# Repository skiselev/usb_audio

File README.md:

# Compact USB Audio Adapter

## Introduction
I was looking for a USB audio adapter for my Intel Galileo projects, and surprisingly I was not able to find a compact USB audio adapter which will offer line input or digital (optical) input and output. Most USB audio dongles available on the market are intended to be used with a headset and only offer monophonic microphone input. One exception was Behringer UCA202 which is bulky for my projects. And so I've designed this adapter.

## Overview
This USB Audio adapter can be used with small SBCs like Intel Galileo, Raspberry Pi, or BeagleBone Black to provide high quality audio input and output. Its size is only 2.1 x 1.6 inches (53.44 x 40.74 mm). This USB Audio adapter will also work with regular PCs, Android based smartphones and tablets, or almost everything else that supports USB audio. It is based on popular Texas Instruments (was Burr Brown) PCM2902C, and schematic mostly follows Texas Instrument's reference design.

### Photos
#### Top side

#### Bottom side

## Design
As mentioned above the main component is Texas Instruments PCM2902 USB audio codec IC (U1). Additionally the circuit uses Texas Instruments REG103UA LDO IC for conditioning power for the analog circuitry (U2) and a pair of dual channel operational amplifier ICs that work as low pass filters for input and output (U5 and U6).

### Schematic and PCB Layout

[Schematic - Version 2.0](KiCad/USB_Audio-Schematic-2.0.pdf)

[PCB Layout - Version 2.0](KiCad/USB_Audio-Board-2.0.pdf)

### Design Modifications and Components' Substitution
There is a lot of flexibility in the design:
* The USB audio codec IC (U1) can be PCM2902, PCM2906, PCM2900, and PCM2904.
  * PCM2902 and PCM2906 provide S/PDIF digital interface. PCM2900 and PCM2904 do not provide it.
  * The difference between PCM2902 and PCM2906 or between PCM2900 and PCM2904 is very subtle: PCM2900 and PCM2902 specify 100mA as Maxpower value in USB descriptor, while PCM2904 and PCM2906 specify 500mA. Operating systems should be using Maxpower values to estimate power consumption by the attached USB devices and disconnect USB devices if host is unable to supply enough power.
  * If using codec without S/PDIF support the components related to optical input and output should not be mounted.
  * I used the latest PCM290xC revision. Other, older revisions don't differ significantly and can be used as well.
* The REG103 LDO (U2) is optional and can be removed to lower the cost at some audio quality degradation. It is also possible to replace it with cheaper LDO with minor schematic and PCB modifications.
* The design uses high-speed operational amplifiers. Either one of these op amps or both can be bypassed, leaving just 100 ohm / 10 uF capacitors for audio coupling. It is also possible to use other compatible operational amplifiers (important characteristics: single power supply 3.3V, rail-to-rail)
* Both input and output parts are optional. For example if only ADC part is needed, no need to assemble components related to audio output. Same applies for DAC only (audio output only) use. In this case I suggest grounding audio inputs of PCM2902 to avoid noise.
* The PCB supports two options for connecting to USB:
  * Using Micro USB connector
  * Using 5-pin header (it is also possible to solder a USB cable directly to the board instead of this header).
* Volume control buttons are optional

### Assembly Notes
Due to project's size and component availability the project mostly uses SMT components. I used through hole components for components that are subject to physical stress (connectors and buttons). It it is not too difficult to solder SMT components it with some practice. Here are some tips:

* Have a well lighten workspace.
* Use a low power (25W or so) soldering iron with thin tip, better yet a temperature controlled soldering station. Keep the tip of soldering iron clean.
* Use thin solder with flux. Have some desoldering braid to remove accidental solder bridges or excess solder.
* I found it convenient first to put some solder on a first pad of a component (or on two opposite pads in case of an IC. When put the component using tweezers and heat the pad at the same time. Next double check component orientation and solder remaining pads. Note that diodes and tantalum capacitors are polarized, so the orientation is important.
* Solder ICs first, next solder micro USB connector.
* After that solder all the resistors, inductor, and smaller (0603 and 0805) capacitors on the top side, going from ICs to sides of the board.
* Solder Schottky diode, LED, crystal resonator, and tantalum capacitors. Make sure to check that they are oriented properly.
* Turn the board up side down, and solder resistors and the capacitors on the bottom side.
* Finally solder through hole components: connectors, optical modules, buttons.
* Clean the flux remains with some alcohol. (Be careful not to get alcohol/flux inside optical modules, or maybe solder them after cleaning the board).
* Search the Internet for SMT soldering tutorials.

### Bill of Materials
[USB Audio project on Mouser.com](http://www.mouser.com/ProjectManager/ProjectDetail.aspx?AccessID=4c01b1b0e1) - View and order all components except of the PCB, screws and nuts.

[USB Audio project on OSH Park](http://oshpark.com/shared_projects/Dffqy1VF) - View and order PCB.

Component type     | Reference | Description                                 | Quantity | Possible sources and notes
------------------ | --------- | ------------------------------------------- | -------- | --------------------------
PCB                |           | USB Audio PCB - V2                          | 1        | Order at [OSH Park](http://oshpark.com/shared_projects/Dffqy1VF) or from any other PCB manufacturer using Gerber files from [gerber](gerber) folder.
Capacitor          | C1 - C3   | 22pF C0G SMT 0603 capacitor                 | 3        | Mouser [77-VJ0603A220JXACBC](https://www.mouser.com/ProductDetail/77-VJ0603A220JXACBC). Note: C3 is not needed if not implementing optical S/PDIF input.
Capacitor          | C4 - C7   | 330pF C0G SMT 0805 capacitor                | 4        | Mouser [77-VJ0805A331KXACBC](https://www.mouser.com/ProductDetail/77-VJ0805A331KXACBC)
Capacitor          | C8 - C11  | 1.8nF C0G SMT 0805 capacitor                | 4        | Mouser [81-GRM215C1H182JA01D](https://www.mouser.com/ProductDetail/81-GRM215C1H182JA01D)
Capacitor          | C12, C13  | 100nF X7R SMT 0805 capacitor                | 2        | Mouser [80-C0805C104K3R7210](https://www.mouser.com/ProductDetail/80-C0805C104K3R7210]. Note: These capacitor are not needed if not implementing optical S/PDIF input and output.
Capacitor          | C14 - C20 | 1uF X7R SMT 0805 capacitor                  | 7        | Mouser [80-C0805C105K4R](https://www.mouser.com/ProductDetail/80-C0805C105K4R]
Capacitor          | C21 - C30 | 10uF tantalum SMT capacitor                 | 10       | Mouser [74-593D106X9016A2TE3](https://www.mouser.com/ProductDetail/74-593D106X9016A2TE3)
Capacitor          | C31, C32  | 220uF tantalum SMT capacitor                | 2        | Mouser [581-TLNT227M010R1300](https://www.mouser.com/ProductDetail/581-TLNT227M010R1300). Note: Use the recommended value if driving low impedance loads (for example headphones). For high impedance loads (e.g. line output connected to an amplifier) cheaper 10uF capacitors can be used. See previous line for part number.
Schottky Diode     | D1        | Schottky diode with low voltage drop (350mV) | 1       | Mouser [771-PMEG2010ER115](https://www.mouser.com/ProductDetail/771-PMEG2010ER115)
LED                | D2        | 0603 LED                                    | 1        | Mouser [78-VLMTG1300-GS08](https://www.mouser.com/ProductDetail/78-VLMTG1300-GS08). Any color can be used :-) The suggested part is "pure" green. It is too bright to my taste, so if using it consider increasing value of R8. Or use "conventional" green and save a few cents.
Inductor           | L1        | 47uH SMT 0805 inductor                      | 1        | Mouser [963-LBR2012T470K](https://www.mouser.com/ProductDetail/963-LBR2012T470K). Note: This inductor is not needed if not implementing optical S/PDIF input.
Connector          | P1        | Micro USB receptacle with through hole pegs | 1        | Mouser [649-10118194-0001LF](https://www.mouser.com/ProductDetail/649-10118194-0001LF). Note: Use either P1 or P2
Connector          | P2        | Pin Header 5x1, 2.54 mm lead spacing        | 1        | Mouser [649-68000-105HLF](https://www.mouser.com/ProductDetail/649-68000-105HLF). Note: Use either P1 or P2
Connector          | P3        | 3.5 mm stereo audio jack, blue              | 1        | Mouser [806-STX-31203B284C](https://www.mouser.com/ProductDetail/806-STX-31203B284C)
Connector          | P4        | 3.5 mm stereo audio jack, green             | 1        | Mouser [806-STX-31203B577C](https://www.mouser.com/ProductDetail/806-STX-31203B577C)
Resistor           | R1 - R3   | 2.2 ohm 1% SMT 0603 resistor                | 3        | Mouser [71-CRCW0603-2.2-E3](https://www.mouser.com/ProductDetail/71-CRCW0603-2.2-E3). Note: For R2 and R3 use the recommended value if driving low impedance loads. For high impedance load resistance can be increased to 100 ohm. See R6, R7 line for part number.
Resistor           | R4, R5    | 22 ohm 1% SMT 0603 resistor                 | 2        | Mouser [71-CRCW0603-22-E3](https://www.mouser.com/ProductDetail/71-CRCW0603-22-E3)
Resistor           | R6, R7    | 100 ohm 1% SMT 0603 resistor                | 2        | Mouser [71-CRCW0603100RFKEB](https://www.mouser.com/ProductDetail/71-CRCW0603100RFKEB)
Resistor           | R8        | 470 ohm 1% SMT 0603 resistor                | 1        | Mouser [71-CRCW0603470RFKEB](https://www.mouser.com/ProductDetail/71-CRCW0603470RFKEB)
Resistor           | R9 - R12  | 1.5 Kohm 1% SMT 0603 resistor               | 4        | Mouser [71-CRCW0603-1.5K-E3](https://www.mouser.com/ProductDetail/71-CRCW0603-1.5K-E3)
Resistor           | R13 - R16 | 3.9 Kohm 1% SMT 0603 resistor               | 4        | Mouser [71-CRCW0603-3.9K-E3](https://www.mouser.com/ProductDetail/71-CRCW0603-3.9K-E3)
Resistor           | R17 - R24 | 12 Kohm 1% SMT 0603 resistor                | 8        | Mouser [71-CRCW0603-12K-E3](https://www.mouser.com/ProductDetail/71-CRCW0603-12K-E3)
Resistor           | R25       | 13 Kohm 1% SMT 0603 resistor                | 1        | Mouser [71-CRCW0603-13K-E3](https://www.mouser.com/ProductDetail/71-CRCW0603-13K-E3)
Resistor           | R26       | 27 Kohm 1% SMT 0603 resistor                | 1        | Mouser [71-CRCW0603-27K-E3](https://www.mouser.com/ProductDetail/71-CRCW0603-27K-E3)
Resistor           | R27       | 1 Mohm 1% SMT 0603 resistor                 | 1        | Mouser [71-CRCW06031M00FKEB](https://www.mouser.com/ProductDetail/71-CRCW06031M00FKEB)
Switch             | SW1 - SW3 | 6 mm x 6 mm tactile switch                  | 3        | Mouser [653-B3F-1050](https://www.mouser.com/ProductDetail/653-B3F-1050)
Switch Key Top     | SW1       | 4 mm x 6 mm tactile switch key top, red     | 1        | Mouser [653-B32-1080](https://www.mouser.com/ProductDetail/653-B32-1080)
Switch Key Top     | SW2       | 4 mm x 6 mm tactile switch key top, green   | 1        | Mouser [653-B32-1050](https://www.mouser.com/ProductDetail/653-B32-1050)
Switch Key Top     | SW3       | 4 mm x 6 mm tactile switch key top, blue    | 1        | Mouser [653-B32-1040](https://www.mouser.com/ProductDetail/653-B32-1040)
Integrated Circuit | U1        | Texas Instruments PCM2902C                  | 1        | Mouser [595-PCM2902CDB](https://www.mouser.com/ProductDetail/595-PCM2902CDB)
Integrated Circuit | U2        | Texas Instruments REG103UA-A                | 1        | Mouser [595-REG103UA-A](https://www.mouser.com/ProductDetail/595-REG103UA-A)
Optical Receiver Module |  U3  | Everlight PLR135/T8                         | 1        | Mouser [638-PLR135T8](https://www.mouser.com/ProductDetail/638-PLR135T8). Note: This module is not needed if not implementing optical S/PDIF input.
Optical Transmitter Module | U4 | Everlight PLT133/T8                        | 1        | Mouser [638-PLT133T8](https://www.mouser.com/ProductDetail/638-PLT133T8).  Note: This module is not needed if not implementing optical S/PDIF output.
Integrated Circuit | U5        | Texas Instruments OPA2353                   | 1        | Mouser [595-OPA2353UA](https://www.mouser.com/ProductDetail/595-OPA2353UA)
Integrated Circuit | U6        | Analog Devices AD8656                       | 1        | Mouser [584-AD8656ARZ](https://www.mouser.com/ProductDetail/584-AD8656ARZ)
Crystal Resonator  | X1        | 12 MHz                                      | 1        | Mouser [774-445C25D12M00000](https://www.mouser.com/ProductDetail/774-445C25D12M00000)

### 3D Printed Case Parts

Component type     | Description                                 | Quantity | Possible sources and notes
------------------ | ------------------------------------------- | -------- | --------------------------
3D Printed Part    | USB Audio Case Top                          | 1        | 3D Print [USB Audio Case Top](printed_parts/USB_Audio_Case_Top.stl)
3D Printed Part    | USB Audio Case Bottom                       | 1        | 3D Print [USB Audio Case Bottom](printed_parts/USB_Audio_Case_Bottom.stl)
Screw              | M3 x 10mm socket cap screw                  | 2        | Fastenal [MS2510010A20000](https://www.fastenal.com/products/details/MS2510010A20000)
Nut                | M3 square nut                               | 2        | Fastenal [0161907](https://www.fastenal.com/products/details/0161907)

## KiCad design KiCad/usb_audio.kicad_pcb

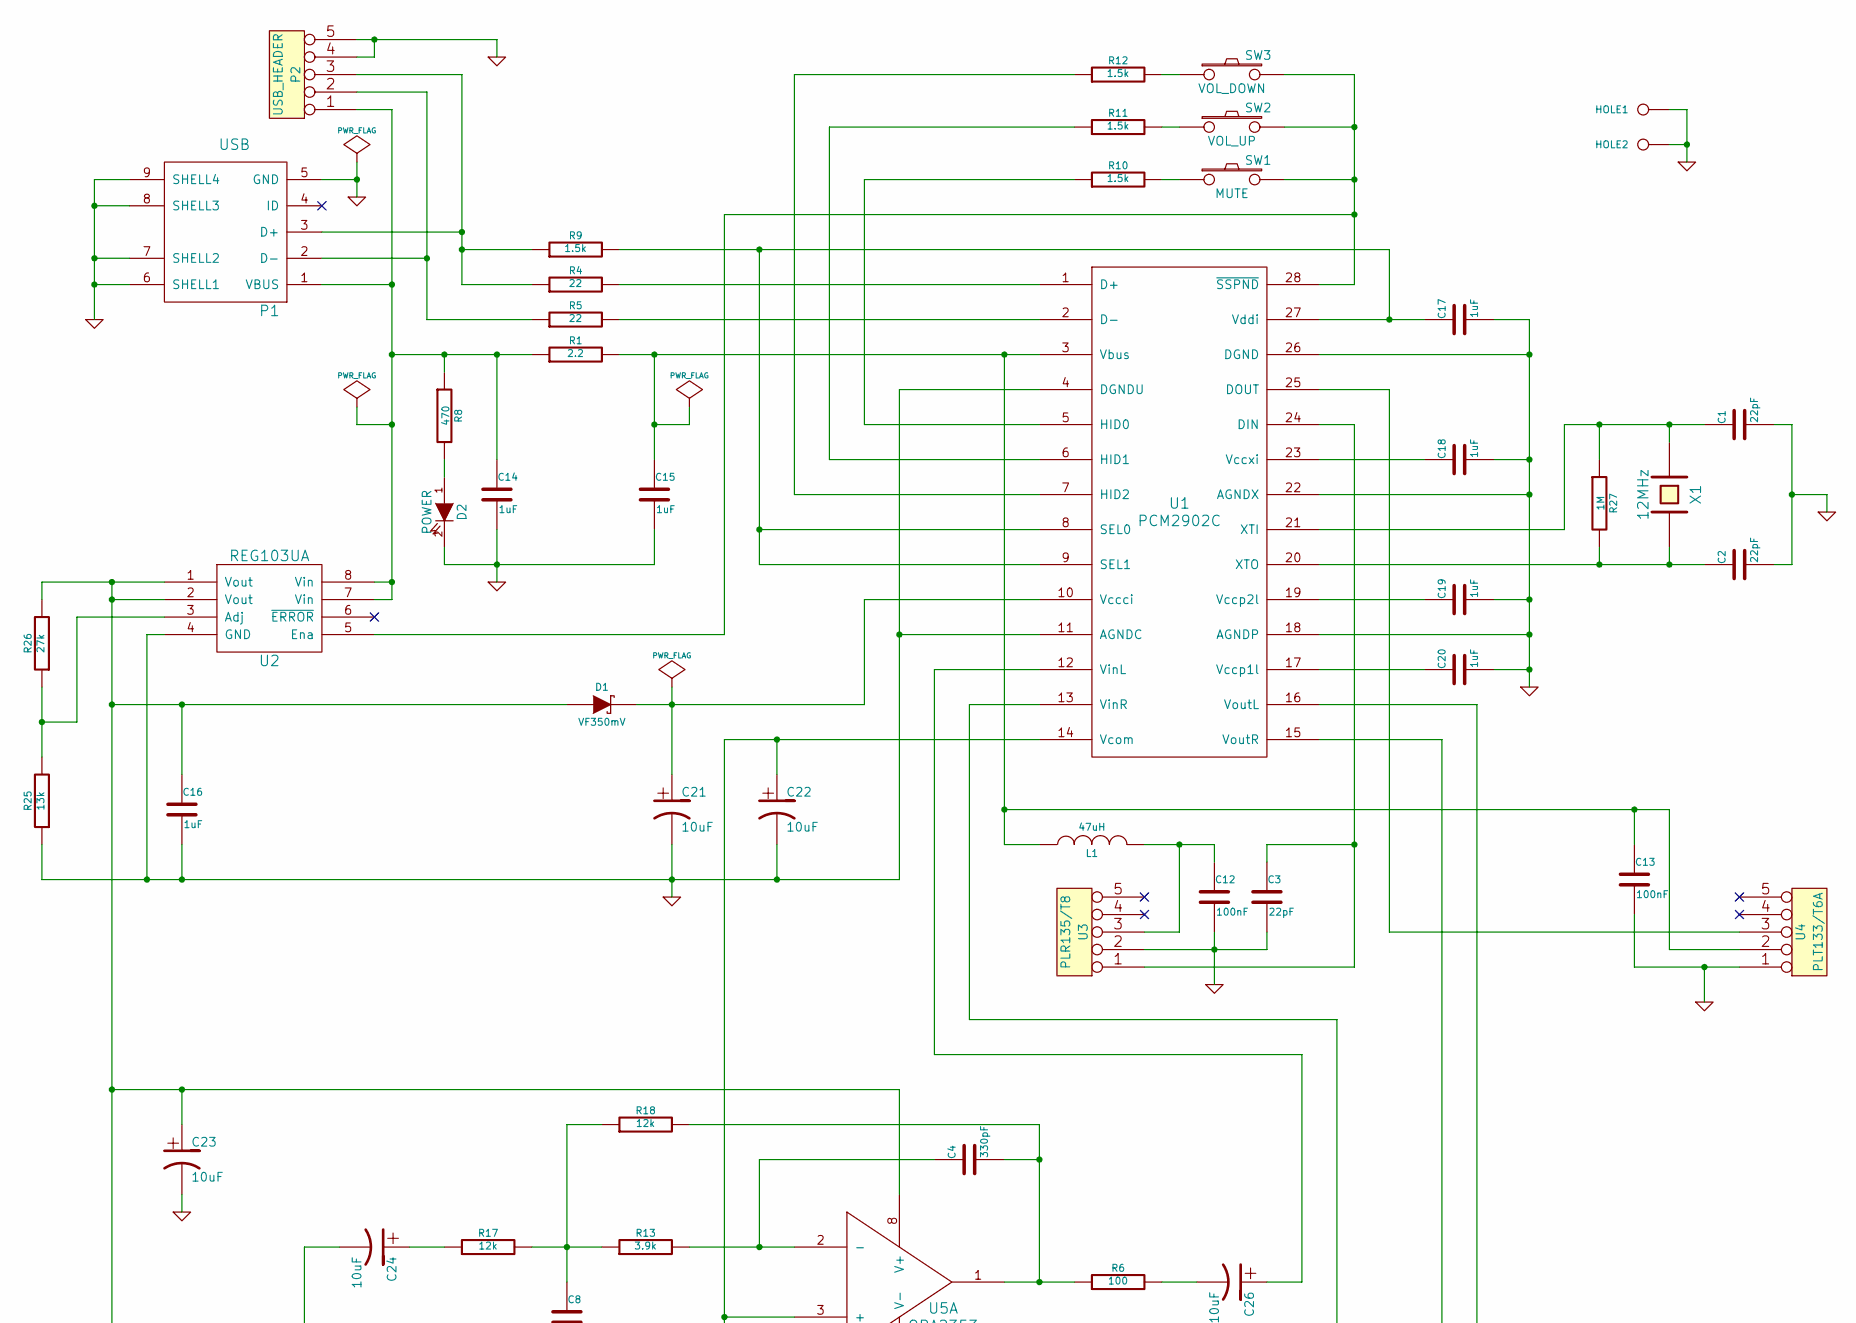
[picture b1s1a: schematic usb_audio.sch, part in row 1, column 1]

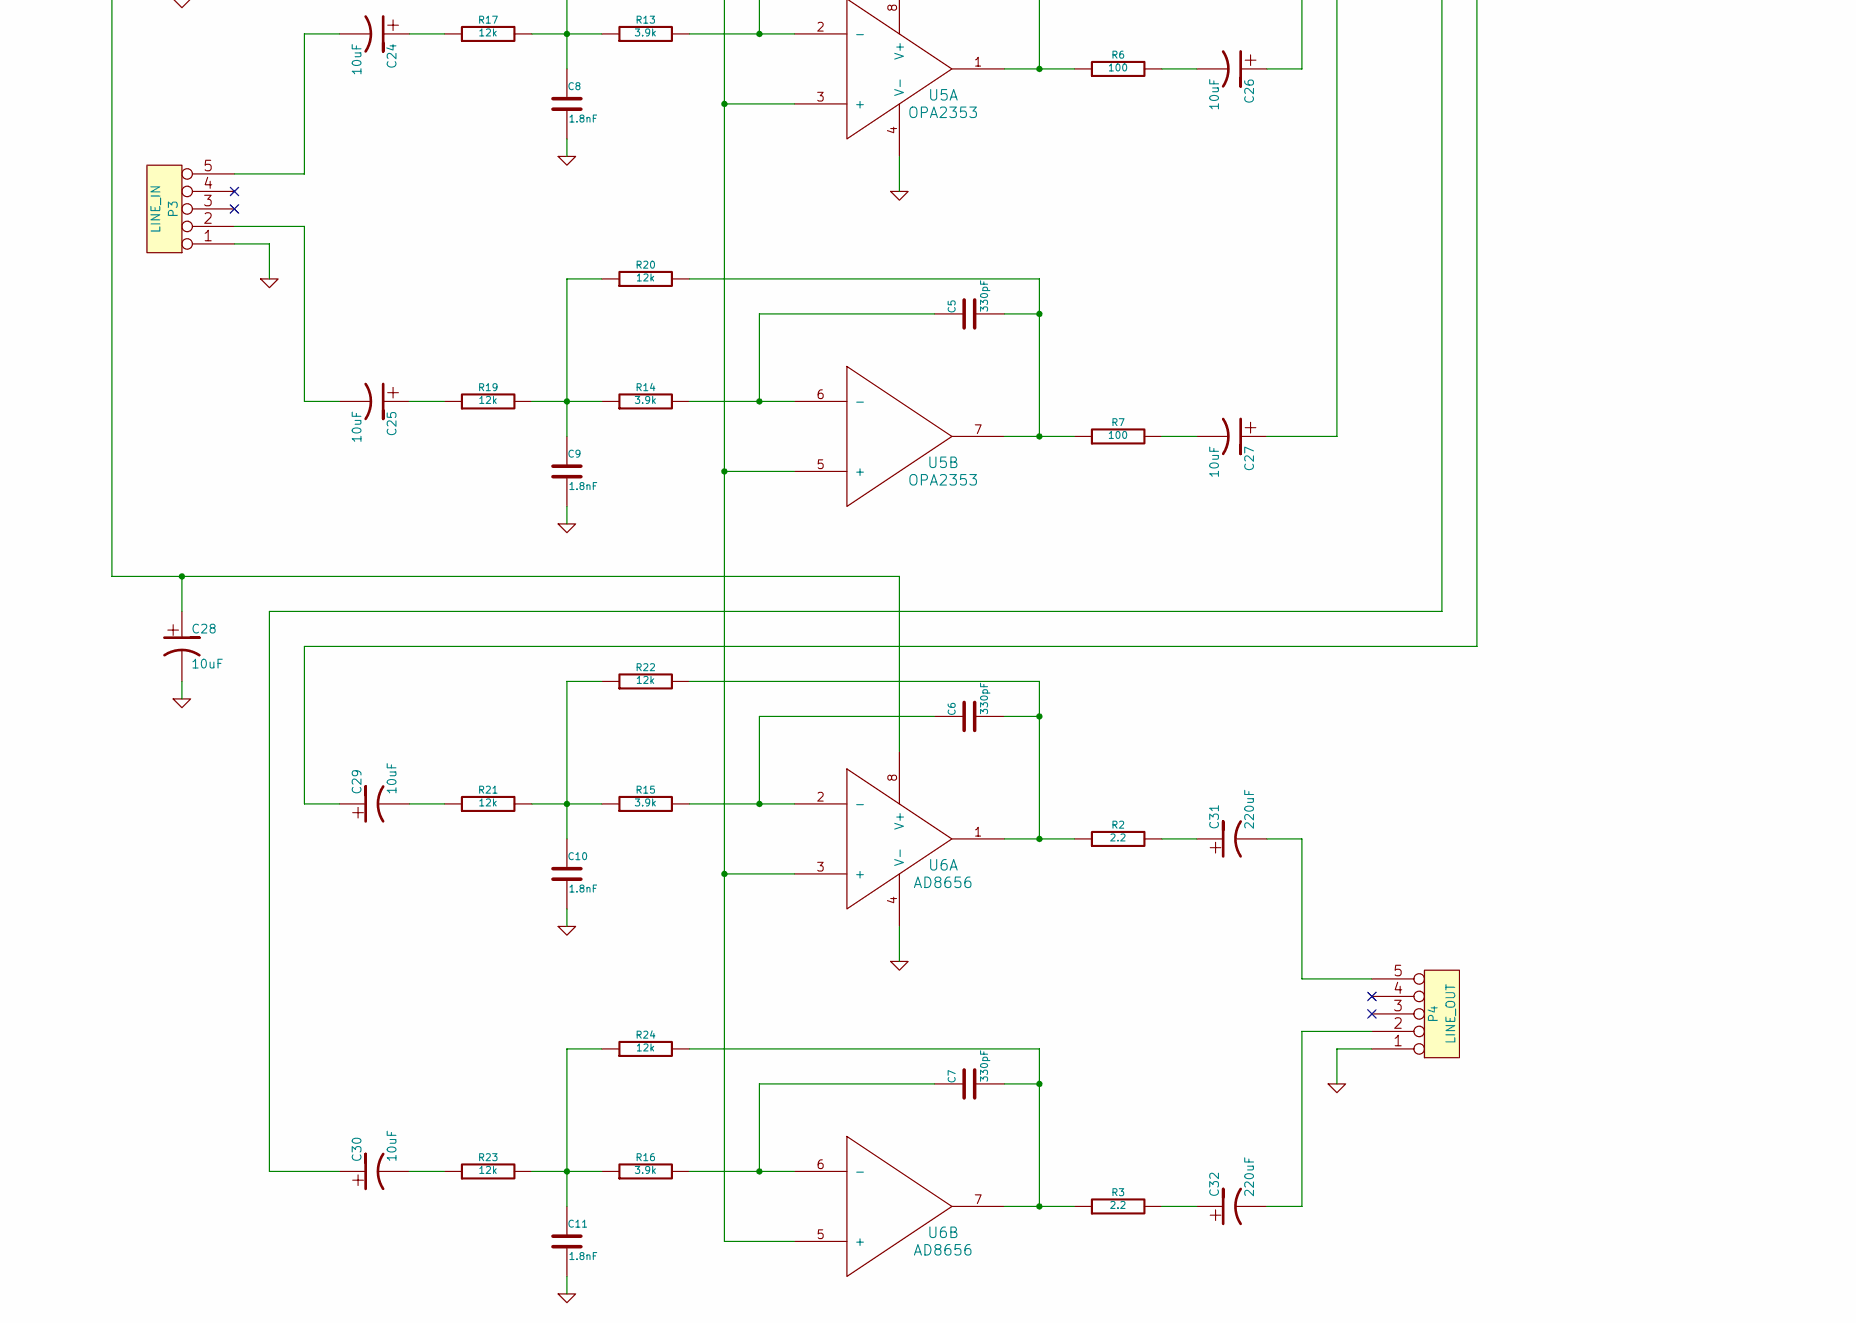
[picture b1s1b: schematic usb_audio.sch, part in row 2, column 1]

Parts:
C1, C2, C3: 22pF
C4, C5, C6, C7: 330pF
C8, C9, C10, C11: 1.8nF
C12, C13: 100nF
C14, C15, C16, C17, C18, C19, C20: 1uF
C21, C22, C23, C24, C25, C26, C27, C28, C29, C30: 10uF
C31, C32: 220uF
D1: VF350mV
D2: POWER
HOLE1, HOLE2: CONN_1
L1: 47uH
P1: USB
P2: USB_HEADER
P3: LINE_IN
P4: LINE_OUT
R1, R2, R3: 2.2
R4, R5: 22
R6, R7: 100
R8: 470
R9, R10, R11, R12: 1.5k
R13, R14, R15, R16: 3.9k
R17, R18, R19, R20, R21, R22, R23, R24: 12k
R25: 13k
R26: 27k
R27: 1M
SW1: MUTE
SW2: VOL_UP
SW3: VOL_DOWN
U1: PCM2902C
U2: REG103UA
U3: PLR135/T8
U4: PLT133/T6A
U5: OPA2353
U6: AD8656
X1: 12MHz

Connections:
GND: C1.2, C2.2, C3.2, C8.2, C9.2, C10.2, C11.2, C12.2, C13.2, C14.2, C15.2, C16.2, C17.2, C18.2, C19.2, C20.2, C21.2, C22.2, C23.2, C28.2, D2.2 (K), HOLE1.1, HOLE2.1, P1.5 (GND), P1.6 (SHELL1), P1.7 (SHELL2), P1.8 (SHELL3), P1.9 (SHELL4), P2.4, P2.5, P3.1, P4.1, R25.1, U1.4 (DGNDU), U1.11 (AGNDC), U1.18 (AGNDP), U1.22 (AGNDX), U1.26 (DGND), U2.4 (GND), U3.2, U4.1, U5.4 (V-), U6.4 (V-)
unnamed: C5.2, R7.1, R20.2, U5.7
unnamed: C5.1, R14.2, U5.6 (-)
unnamed: C26.2, R6.2
unnamed: C27.2, R7.2
unnamed: C4.2, R6.1, R18.2, U5.1
unnamed: C4.1, R13.2, U5.2 (-)
unnamed: C29.2, R21.1
unnamed: C32.1, R3.2
unnamed: C30.2, R23.1
unnamed: C31.1, R2.2
unnamed: U1.25 (DOUT), U4.3
unnamed: C24.1, R17.1
unnamed: C25.1, R19.1
unnamed: C8.1, R13.1, R17.2, R18.1
unnamed: C9.1, R14.1, R19.2, R20.1
unnamed: C16.1, C23.1, C28.1, D1.1 (A), R26.2, U2.1 (Vout), U2.2 (Vout), U5.8 (V+), U6.8 (V+)
unnamed: R25.2, R26.1, U2.3 (Adj)
unnamed: C21.1, D1.2 (K), U1.10 (Vccci)
unnamed: C6.1, R15.2, U6.2 (-)
unnamed: C6.2, R2.1, R22.2, U6.1
unnamed: C7.1, R16.2, U6.6 (-)
unnamed: C7.2, R3.1, R24.2, U6.7
unnamed: C10.1, R15.1, R21.2, R22.1
unnamed: C11.1, R16.1, R23.2, R24.1
unnamed: C29.1, U1.16 (VoutL)
unnamed: R12.1, U1.7 (HID2)
unnamed: R10.1, U1.5 (HID0)
unnamed: R11.1, U1.6 (HID1)
unnamed: SW1.2, SW2.2, SW3.2, U1.28 (~SSPND), U2.5 (Ena)
unnamed: R12.2, SW3.1
unnamed: R11.2, SW2.1
unnamed: R10.2, SW1.1
unnamed: P1.3 (D+), P2.3, R4.1, R9.1
unnamed: D2.1 (A), R8.2
unnamed: C17.1, R9.2, U1.8 (SEL0), U1.9 (SEL1), U1.27 (Vddi)
unnamed: C14.1, P1.1 (VBUS), P2.1, R1.1, R8.1, U2.7 (Vin), U2.8 (Vin)
unnamed: P1.2 (D-), P2.2, R5.1
unnamed: C30.1, U1.15 (VoutR)
unnamed: C26.1, U1.12 (VinL)
unnamed: C27.1, U1.13 (VinR)
unnamed: C22.1, U1.14 (Vcom), U5.3 (+), U5.5 (+), U6.3 (+), U6.5 (+)
unnamed: R4.2, U1.1 (D+)
unnamed: R5.2, U1.2 (D-)
unnamed: C31.2, P4.5
unnamed: C25.2, P3.2
unnamed: C24.2, P3.5
unnamed: C32.2, P4.2
unnamed: C18.1, U1.23 (Vccxi)
unnamed: C19.1, U1.19 (Vccp2l)
unnamed: C20.1, U1.17 (Vccp1l)
unnamed: C3.1, U1.24 (DIN), U3.1
unnamed: C12.1, L1.2, U3.3
unnamed: C13.1, C15.1, L1.1, R1.2, U1.3 (Vbus), U4.2
unnamed: C1.1, R27.1, U1.21 (XTI), X1.1
unnamed: C2.1, R27.2, U1.20 (XTO), X1.2

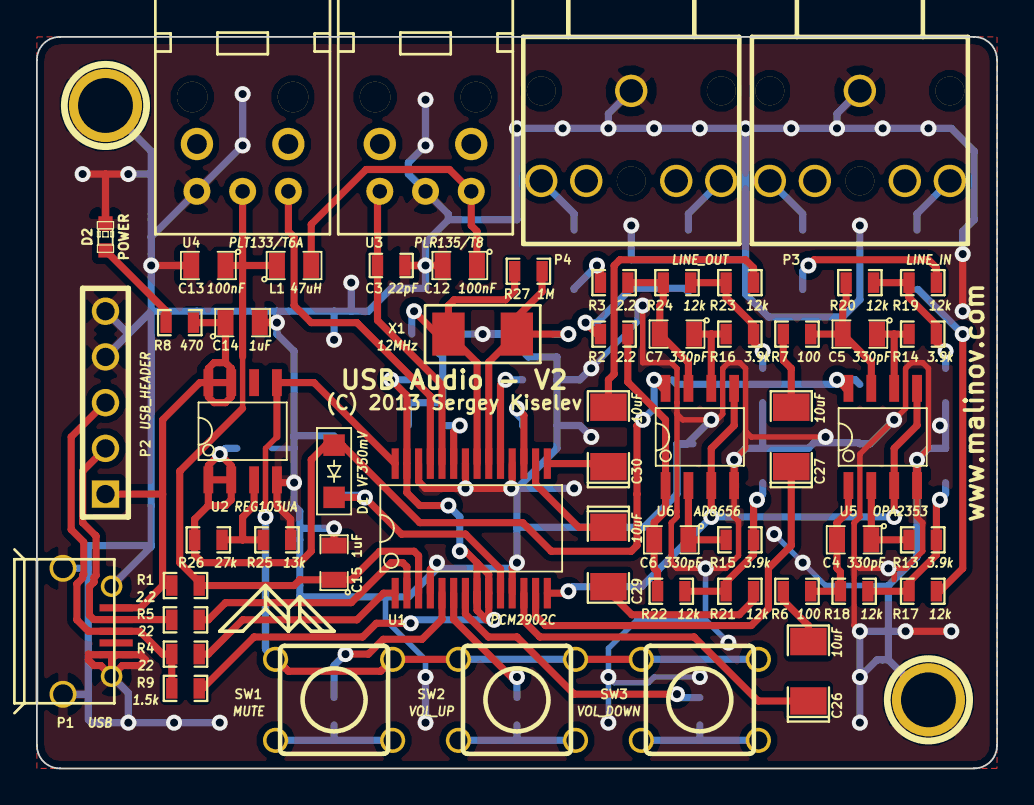
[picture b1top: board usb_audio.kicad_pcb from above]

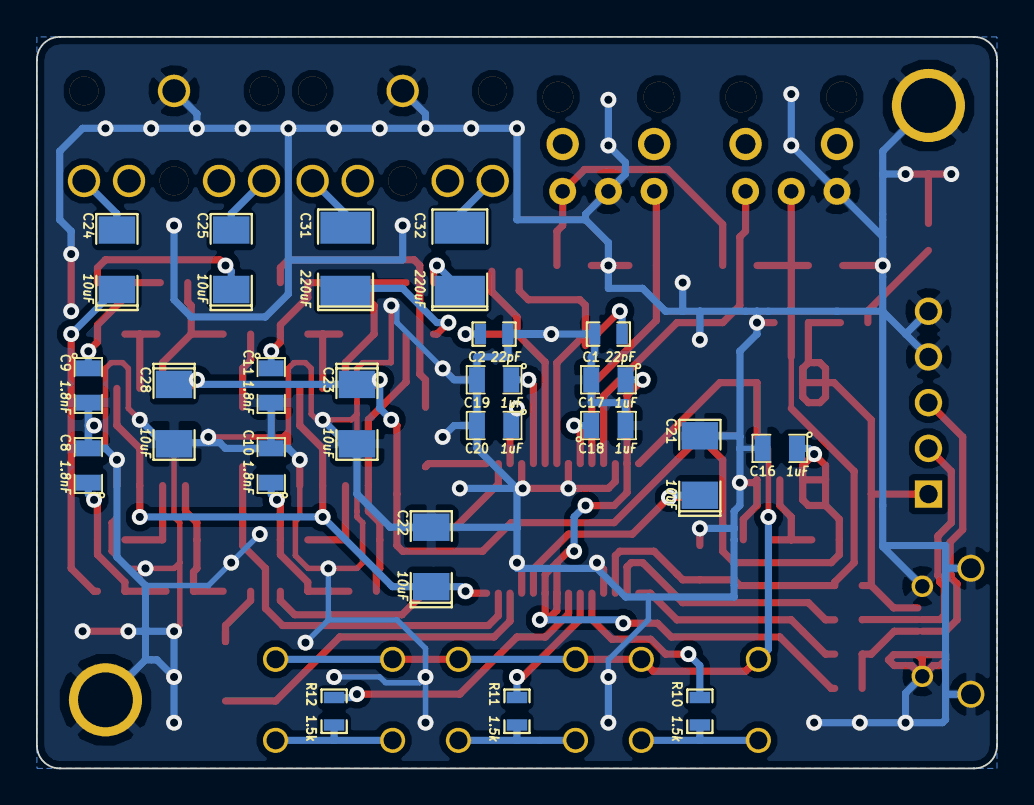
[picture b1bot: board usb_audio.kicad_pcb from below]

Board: 2 copper layers, 53.3 x 40.6 mm, 78 parts (22 on the bottom side), 56 nets.

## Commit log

2019-12-10 Add 3D printed case
2019-12-10 Add KiCad files
2019-12-10 Add PDFs with schematic and PCB layout
2019-12-10 Add Gerber files
2019-12-10 Add project photos

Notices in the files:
KiCad/usb_audio.kicad_pcb:
(C) 2013 Sergey Kiselev
